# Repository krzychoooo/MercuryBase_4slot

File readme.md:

# MercuryBase_4slot

The idea behind the MERCURY project is to create a controller that doesn't contain any peripherals.   
The required peripheral modules can be inserted into the baseboard.
<picture></picture>   
<picture></picture>   
The housing is adapted for mounting on a DIN35 rail.  

The current list of available modules is provided below.
## Links:   
Hardware:   
1. <a href="https://github.com/krzychoooo/Mercury_PCB_Ethernet_V100" target="_blank">Mercury_PCB_Ethernet_V100</a>
2. <a href="https://github.com/krzychoooo/Mercury_PCB_NPNOUT_x8_V100" target="_blank">Mercury_PCB_NPNOUT_x8_V100</a>
3. <a href="https://github.com/krzychoooo/Mercury_PCB_Relay3x_V100" target="_blank">Mercury_PCB_Relay3x_V100</a>
4. <a href="https://github.com/krzychoooo/Mercury_PCB_UOut1-10V_V100" target="_blank">Mercury_PCB_UOut1-10V_V100</a>   
5. <a href="https://github.com/krzychoooo/Mercury_PCB_Inputx5_V100" target="_blank">Mercury_PCB_Inputx5_V100</a>   

Soft:   
1. <a href="https://github.com/krzychoooo/Mercury_Soft_UOut1-10V_V100" target="_blank">Mercury_Soft_UOut1-10V_V100</a>
2. <a href="https://github.com/krzychoooo/Mercury_Soft_RS485_V100" target="_blank">Mercury_Soft_RS485_V100</a>
3. <a href="https://github.com/krzychoooo/Mercury_Soft_Relay_x3_V100" target="_blank">Mercury_Soft_Relay_x3_V100</a>
4. <a href="https://github.com/krzychoooo/Mercury_Soft_Input5x_V1.0.0" target="_blank">Mercury_Soft_Input5x_V1.0.0</a>   

## Custom project.   
You can connect your own custom modules to the structure.   
These can be quickly created using the Kicad template I provided.   
<a href="https://github.com/krzychoooo/MercuryTemplate" target="_blank">Kicad Template</a>    
After loading the template, you'll see a connector in the schematic window along with the network names.   
<picture></picture>   
In the PCB window, you'll see the board outline with the correctly positioned connector.   
<picture></picture>   

## Mechanical Solutions:   
The MERCURY baseboard fits into the DM108-150-14-100AH ​​housing.
<picture></picture>
The housing is adapted for mounting on a DIN35 rail.

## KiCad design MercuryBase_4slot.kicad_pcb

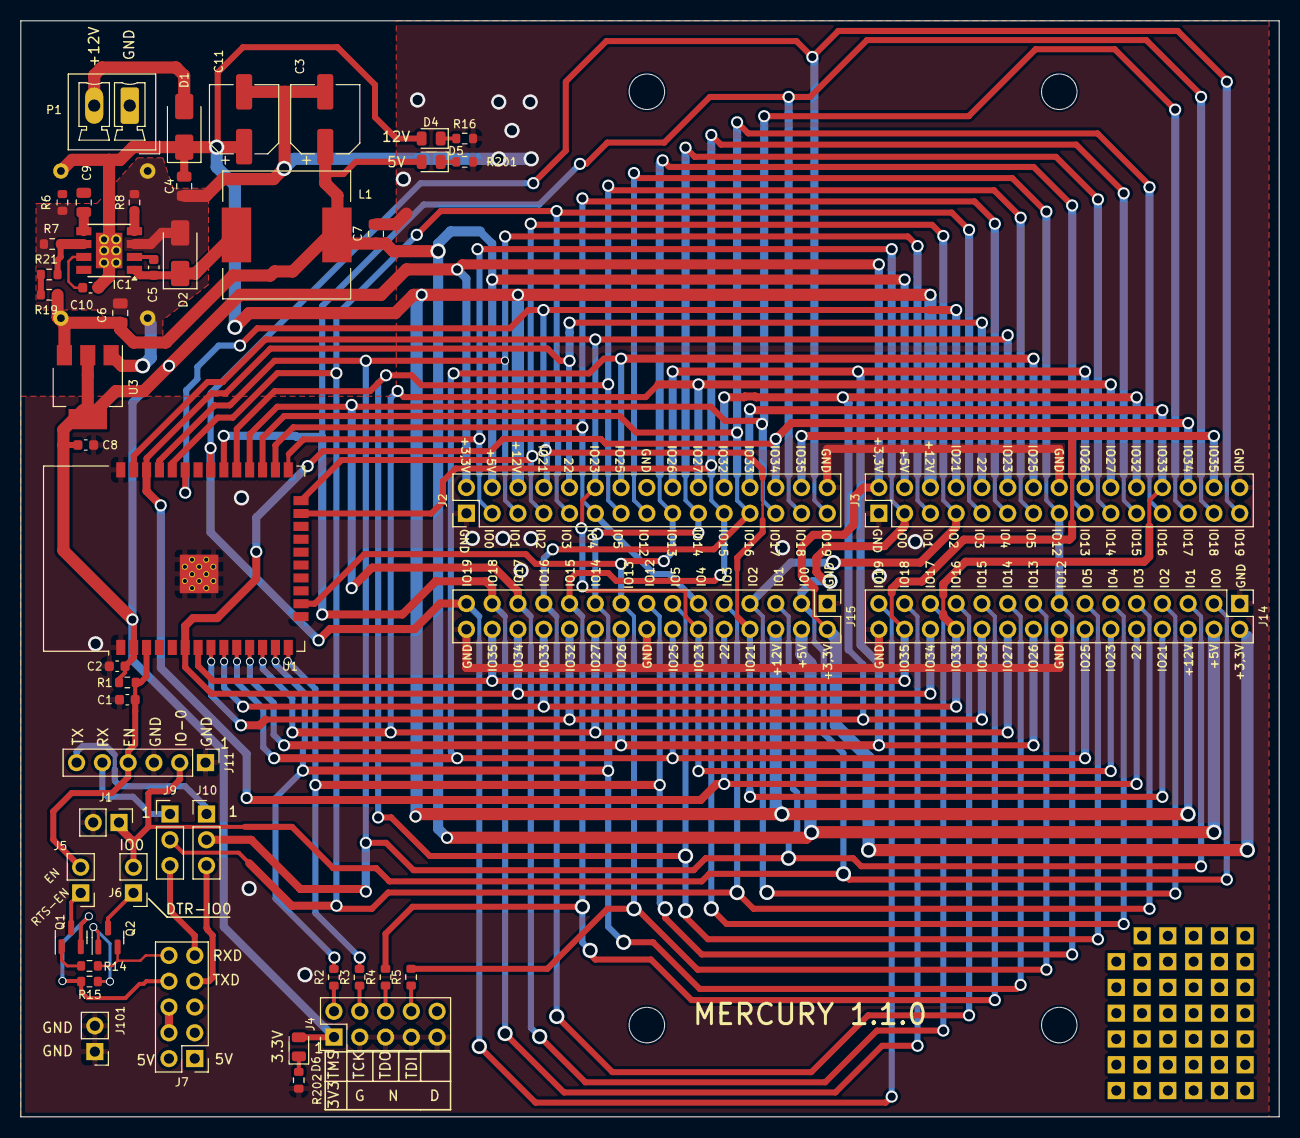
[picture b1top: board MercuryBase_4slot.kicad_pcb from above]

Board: 2 copper layers, 124.0 x 108.0 mm, 52 parts (1 on the bottom side), 56 nets.

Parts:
C1, C2, C5, C8, C10: 100nF/50V; C_0603_1608Metric
C3, C11: 33uF/50V; CP_Elec_6.3x7.7
C4: 4,7uF/50V; C_0805_2012Metric
C6, C7: 22uF/25V; C_0805_2012Metric
C9: 1nF; C_0805_2012Metric
D1, D2: SS56F-DC; D_SMA
D4, D5, D6: LED; LED_0805_2012Metric
IC1: AOZ1283PI; Diodes_SO-8EP
J1, J5, J6: Conn_01x02; PinHeader_1x02_P2.54mm_Vertical
J2, J3, J14, J15: Conn_02x15_Odd_Even; PinHeader_2x15_P2.54mm_Vertical_female
J4, J7: Conn_02x05_Odd_Even; PinHeader_2x05_P2.54mm_Vertical
J9, J10: Conn_01x03; PinHeader_1x03_P2.54mm_Vertical
J11: Conn_01x06; PinHeader_1x06_P2.54mm_Vertical
J101: Conn_01x02_Pin; PinHeader_1x02_P2.54mm_Vertical
J201: Mini360
L1: 22uH; L_12x12mm_H6mm
P1: CONN_01X02; PhoenixContact_MCV_1,5_2-G-3.5_1x02_P3.50mm_Vertical
Q1, Q2: SS8050; SOT-23
R1, R7, R16: 10K; R_0603_1608Metric
R2, R3, R4, R5: 100R; R_0603_1608Metric
R6: 20K; R_0603_1608Metric
R8: 100K; R_0603_1608Metric
R14, R15: 12K; R_0603_1608Metric
R19: 51K; R_0603_1608Metric
R21: 1,2K; R_0603_1608Metric
R201: 2,7K; R_0603_1608Metric
R202: 1,8K; R_0603_1608Metric
U1: ESP32-WROOM-32D
U3: AMS1117-3.3; SOT-223-3_TabPin2

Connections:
+3.3V: C2.1, C8.1, D6.2 (A), J2.2, J3.2, J4.1, J14.2, J15.2, R1.1, U1.2 (VDD), U3.2 (VO)
+5V: C3.1, C6.1, C7.1, D5.2 (A), J2.4, J3.4, J14.4, J15.4, J201.2, L1.2, R19.1, U3.3 (VI)
+12V: C4.1, C10.2, C11.1, D1.1 (K), D4.2 (A), IC1.9 (VIN), J2.6, J3.6, J14.6, J15.6, J201.1
/EN: C1.1, J5.2, J11.4, R1.2, U1.3 (EN)
/IO0: J1.1, J2.3, J3.3, J6.2, J11.2, J14.3, J15.3, U1.25 (IO0)
/IO1: J2.5, J3.5, J10.2, J14.5, J15.5, U1.35 (TXD0/IO1)
/IO2: J2.7, J3.7, J14.7, J15.7, U1.24 (IO2)
/IO3: J2.9, J3.9, J9.2, J14.9, J15.9, U1.34 (RXD0/IO3)
/IO4: J2.11, J3.11, J14.11, J15.11, U1.26 (IO4)
/IO5: J2.13, J3.13, J14.13, J15.13, U1.29 (IO5)
/IO16: J2.23, J3.23, J14.23, J15.23, U1.27 (IO16)
/IO17: J2.25, J3.25, J14.25, J15.25, U1.28 (IO17)
/IO18: J2.27, J3.27, J14.27, J15.27, U1.30 (IO18)
/IO19: J2.29, J3.29, J14.29, J15.29, U1.31 (IO19)
/IO21: J2.8, J3.8, J14.8, J15.8, U1.33 (IO21)
/IO22: J2.10, J3.10, J14.10, J15.10, U1.36 (IO22)
/IO23: J2.12, J3.12, J14.12, J15.12, U1.37 (IO23)
/IO25: J2.14, J3.14, J14.14, J15.14, U1.10 (IO25)
/IO26: J2.18, J3.18, J14.18, J15.18, U1.11 (IO26)
/IO27: J2.20, J3.20, J14.20, J15.20, U1.12 (IO27)
/IO32: J2.22, J3.22, J14.22, J15.22, U1.8 (IO32)
/IO33: J2.24, J3.24, J14.24, J15.24, U1.9 (IO33)
/IO34: J2.26, J3.26, J14.26, J15.26, U1.6 (IO34)
/IO35: J2.28, J3.28, J14.28, J15.28, U1.7 (IO35)
/USB/DTR: J7.10, Q2.2 (E), R14.1
/USB/EN: J5.1, Q1.3 (C)
/USB/IO0: J6.1, Q2.3 (C)
/USB/RTS: J7.8, Q1.2 (E), R15.1
/USB/RXD: J7.9, J9.3
/USB/TXD: J7.7, J10.3
GND: C1.2, C2.2, C3.2, C4.2, C6.2, C7.2, C8.2, C11.2, D2.2 (A), IC1.3 (GND), J1.2, J2.1, J2.16, J2.30, J3.1, J3.16, J3.30, J4.3, J4.5, J4.7, J4.9, J7.5, J11.1, J11.3, J14.1, J14.16, J14.30, J15.1, J15.16, J15.30, J101.1, J101.2, J201.3, J201.4, P1.1, R6.2, R7.2, R8.2, R16.2, R201.2, R202.2, U1.1 (GND), U1.15 (GND), U1.38 (GND), U1.39 (GND), U3.1 (GND)
unnamed: C9.1, R6.1
unnamed: D1.2 (A), P1.2
unnamed: C5.1, D2.1 (K), IC1.1 (LX), L1.1
unnamed: D4.1 (K), R16.1
unnamed: D5.1 (K), R201.1
unnamed: D6.1 (K), R202.1
unnamed: C5.2, IC1.2 (BST)
unnamed: C9.2, IC1.5 (COMP)
unnamed: IC1.6 (FB), R7.1, R21.2
unnamed: IC1.4 (FSW), R8.1
unnamed: C10.1, IC1.7 (SS)
unnamed: J4.2, R2.1
unnamed: J4.4, R3.1
unnamed: J4.6, R4.1
unnamed: J4.8, R5.1
unnamed: J7.4, J7.6
unnamed: J10.1, J11.6
unnamed: J9.1, J11.5
unnamed: Q1.1 (B), R14.2
unnamed: Q2.1 (B), R15.2
unnamed: R19.2, R21.1
TCK: J2.15, J3.15, J14.15, J15.15, R3.2, U1.14 (IO12)
TDI: J2.17, J3.17, J14.17, J15.17, R5.2, U1.16 (IO13)
TDO: J2.21, J3.21, J14.21, J15.21, R4.2, U1.23 (IO15)
TMS: J2.19, J3.19, J14.19, J15.19, R2.2, U1.13 (IO14)

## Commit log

2025-07-02 Version 1.0.0
2025-10-05 first
2025-10-05 dodano schemat pdf
2025-10-05 add readme
2025-10-05 dodano fotkę
2025-10-07 remove MercuryBase_4slot.kicad_pcb
2025-10-07 deleted: MercuryBase_4slot.kicad_pcb
2025-10-07 delpcb_coil
2025-10-07 del plots/
2025-10-07 del test.py
2025-10-07 del testGita.txt
2025-10-07 edit readme
2025-10-08 dodano fotke base8slot
